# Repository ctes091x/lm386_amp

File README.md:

# LM386_Amp

Hello World for KiCad with LM386 audio amplifier

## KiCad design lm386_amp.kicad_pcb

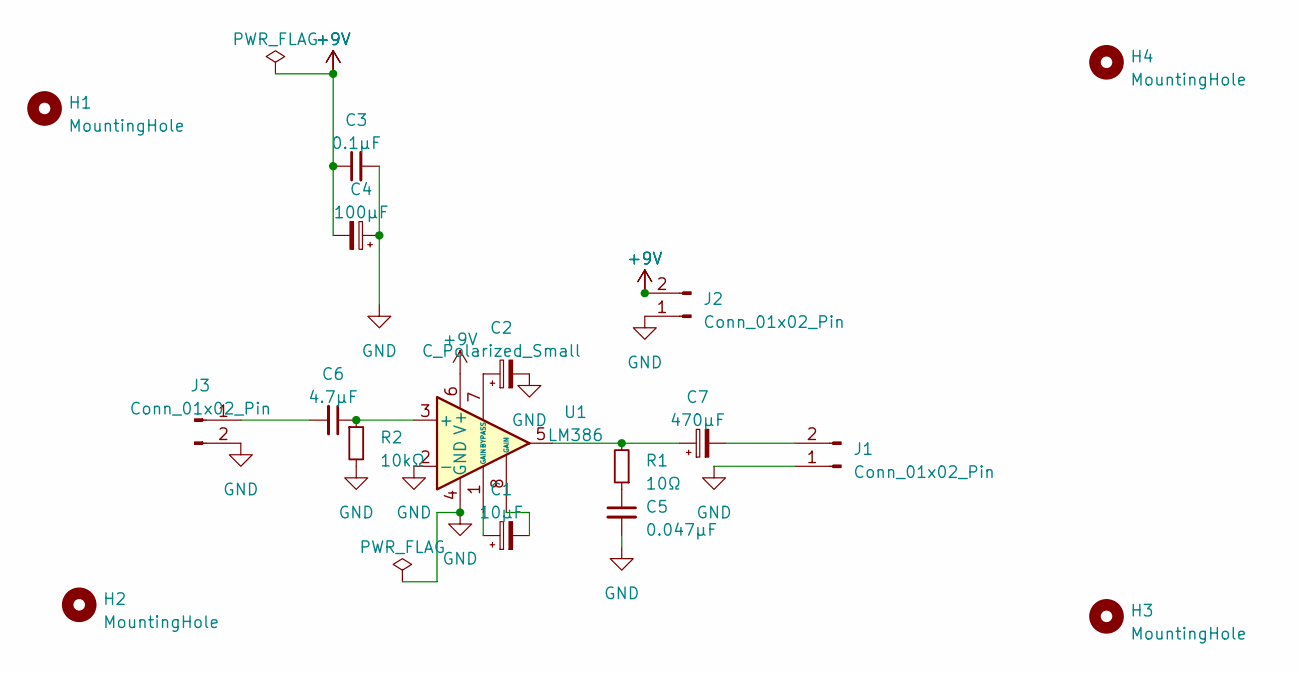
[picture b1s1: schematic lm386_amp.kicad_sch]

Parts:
C1: 10μF; CP_Radial_D5.0mm_P2.50mm
C2: C_Polarized_Small; CP_Radial_D7.5mm_P2.50mm
C3: 0.1μF; C_Disc_D5.0mm_W2.5mm_P5.00mm
C4: 100μF; CP_Radial_D7.5mm_P2.50mm
C5: 0.047μF; C_Disc_D4.7mm_W2.5mm_P5.00mm
C6: 4.7μF; C_Radial_D6.3mm_H5.0mm_P2.50mm
C7: 470μF; CP_Radial_D8.0mm_P2.50mm
H1, H2, H3, H4: MountingHole; MountingHole_3.2mm_M3
J1, J2, J3: Conn_01x02_Pin; PinHeader_1x02_P2.54mm_Vertical
R1: 10Ω; R_Axial_DIN0207_L6.3mm_D2.5mm_P10.16mm_Horizontal
R2: 10kΩ; R_Axial_DIN0207_L6.3mm_D2.5mm_P10.16mm_Horizontal
U1: LM386; DIP-8_W7.62mm_Socket

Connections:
+9V: C3.1, C4.2, J2.2, U1.6 (V+)
GND: C2.2, C3.2, C4.1, C5.2, J1.1, J2.1, J3.2, R2.2, U1.2 (-), U1.4 (GND)
unnamed: C1.1, U1.1 (GAIN)
unnamed: C1.2, U1.8 (GAIN)
unnamed: C5.1, R1.1
unnamed: C7.1, R1.2, U1.5
unnamed: C7.2, J1.2
unnamed: C6.2, J3.1
unnamed: C6.1, R2.1, U1.3 (+)
unnamed: C2.1, U1.7 (BYPASS)

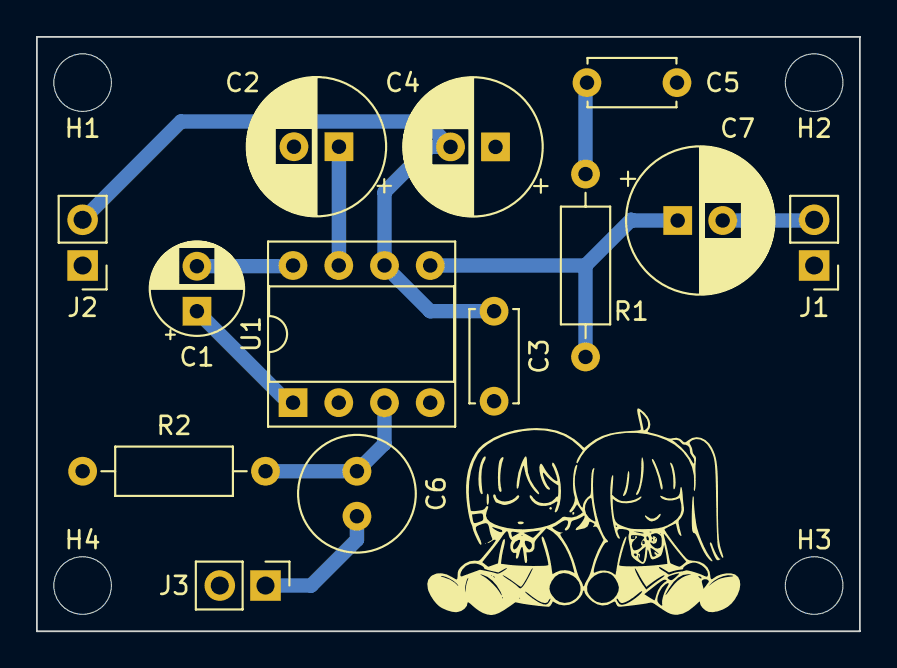
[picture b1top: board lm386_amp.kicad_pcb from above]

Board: 2 copper layers, 45.7 x 33.0 mm, 17 parts (0 on the bottom side), 10 nets.

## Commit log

2023-03-26 init
2023-03-26 feat: schematic and pcb design
